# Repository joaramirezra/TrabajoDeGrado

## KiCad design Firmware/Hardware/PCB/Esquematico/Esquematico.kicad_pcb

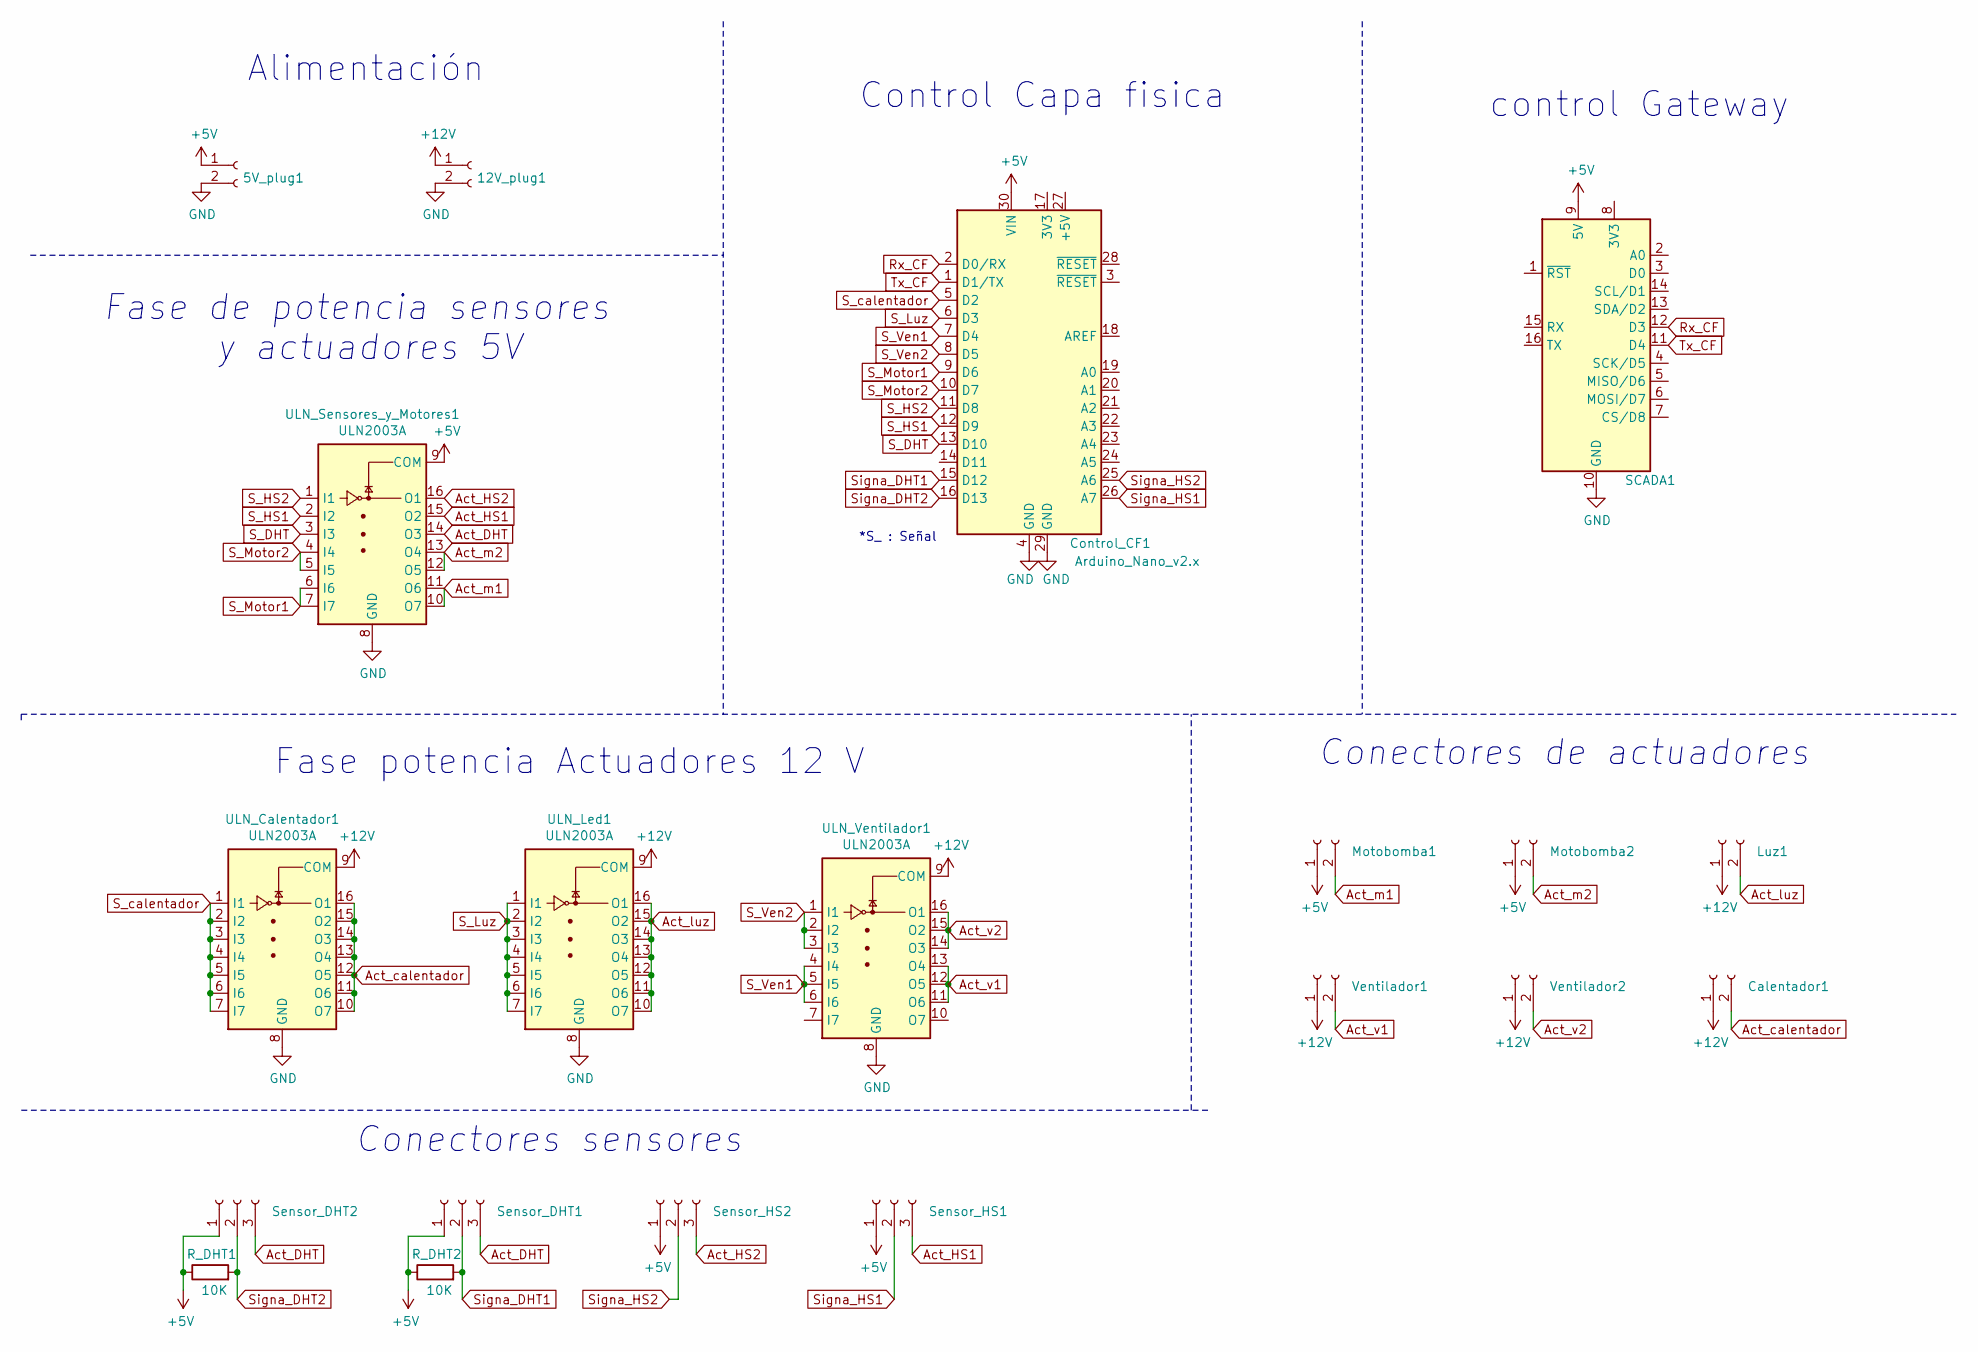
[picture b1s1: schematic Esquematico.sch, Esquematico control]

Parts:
5V_plug1, 12V_plug1: Conn_01x02_Female; TerminalBlock_bornier-2_P5.08mm
Calentador1: Conn_01x02_Female; TerminalBlock_bornier-2_P5.08mm
Control_CF1: Arduino_Nano_v2.x; Arduino_Nano
Luz1: Conn_01x02_Female; TerminalBlock_bornier-2_P5.08mm
Motobomba1, Motobomba2: Conn_01x02_Female; TerminalBlock_bornier-2_P5.08mm
R_DHT1, R_DHT2: 10K; R_Axial_DIN0207_L6.3mm_D2.5mm_P7.62mm_Horizontal
SCADA1: WeMos_D1_mini; WEMOS_D1_mini_light
Sensor_DHT1, Sensor_DHT2: Conn_01x03_Female; TerminalBlock_bornier-3_P5.08mm
Sensor_HS1, Sensor_HS2: Conn_01x03_Female; TerminalBlock_bornier-3_P5.08mm
ULN_Calentador1: ULN2003A; DIP-16_W7.62mm_LongPads
ULN_Led1: ULN2003A; DIP-16_W7.62mm_LongPads
ULN_Sensores_y_Motores1: ULN2003A; DIP-16_W7.62mm_LongPads
ULN_Ventilador1: ULN2003A; DIP-16_W7.62mm_LongPads
Ventilador1, Ventilador2: Conn_01x02_Female; TerminalBlock_bornier-2_P5.08mm

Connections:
+5V: 5V_plug1.1, Control_CF1.30 (VIN), Motobomba1.1, Motobomba2.1, R_DHT1.1, R_DHT2.1, SCADA1.9 (5V), Sensor_DHT1.1, Sensor_DHT2.1, Sensor_HS1.1, Sensor_HS2.1, ULN_Sensores_y_Motores1.9 (COM); also elsewhere on the board
+12V: 12V_plug1.1, Calentador1.1, Luz1.1, ULN_Calentador1.9 (COM), ULN_Led1.9 (COM), ULN_Ventilador1.9 (COM), Ventilador1.1, Ventilador2.1
Act_DHT: Sensor_DHT1.3, Sensor_DHT2.3, ULN_Sensores_y_Motores1.14 (O3); also elsewhere on the board
Act_HS1: Sensor_HS1.3, ULN_Sensores_y_Motores1.15 (O2); also elsewhere on the board
Act_HS2: Sensor_HS2.3, ULN_Sensores_y_Motores1.16 (O1); also elsewhere on the board
Act_calentador: Calentador1.2, ULN_Calentador1.10 (O7), ULN_Calentador1.11 (O6), ULN_Calentador1.12 (O5), ULN_Calentador1.13 (O4), ULN_Calentador1.14 (O3), ULN_Calentador1.15 (O2), ULN_Calentador1.16 (O1)
Act_luz: Luz1.2, ULN_Led1.10 (O7), ULN_Led1.11 (O6), ULN_Led1.12 (O5), ULN_Led1.13 (O4), ULN_Led1.14 (O3), ULN_Led1.15 (O2), ULN_Led1.16 (O1)
Act_m1: Motobomba1.2, ULN_Sensores_y_Motores1.10 (O7), ULN_Sensores_y_Motores1.11 (O6); also elsewhere on the board
Act_m2: Motobomba2.2, ULN_Sensores_y_Motores1.12 (O5), ULN_Sensores_y_Motores1.13 (O4); also elsewhere on the board
Act_v1: ULN_Ventilador1.11 (O6), ULN_Ventilador1.12 (O5), ULN_Ventilador1.13 (O4), Ventilador1.2
Act_v2: ULN_Ventilador1.14 (O3), ULN_Ventilador1.15 (O2), ULN_Ventilador1.16 (O1), Ventilador2.2
GND: 5V_plug1.2, 12V_plug1.2, Control_CF1.4 (GND), Control_CF1.29 (GND), SCADA1.10 (GND), ULN_Calentador1.8 (GND), ULN_Led1.8 (GND), ULN_Sensores_y_Motores1.8 (GND), ULN_Ventilador1.8 (GND); also elsewhere on the board
Rx_CF: Control_CF1.2 (D0/RX), SCADA1.12 (D3)
S_DHT: Control_CF1.13 (D10), ULN_Sensores_y_Motores1.3 (I3); also elsewhere on the board
S_HS1: Control_CF1.12 (D9), ULN_Sensores_y_Motores1.2 (I2); also elsewhere on the board
S_HS2: Control_CF1.11 (D8), ULN_Sensores_y_Motores1.1 (I1); also elsewhere on the board
S_Luz: Control_CF1.6 (D3), ULN_Led1.1 (I1), ULN_Led1.2 (I2), ULN_Led1.3 (I3), ULN_Led1.4 (I4), ULN_Led1.5 (I5), ULN_Led1.6 (I6), ULN_Led1.7 (I7)
S_Motor1: Control_CF1.9 (D6), ULN_Sensores_y_Motores1.6 (I6), ULN_Sensores_y_Motores1.7 (I7); also elsewhere on the board
S_Motor2: Control_CF1.10 (D7), ULN_Sensores_y_Motores1.4 (I4), ULN_Sensores_y_Motores1.5 (I5); also elsewhere on the board
S_Ven1: Control_CF1.7 (D4), ULN_Ventilador1.4 (I4), ULN_Ventilador1.5 (I5), ULN_Ventilador1.6 (I6)
S_Ven2: Control_CF1.8 (D5), ULN_Ventilador1.1 (I1), ULN_Ventilador1.2 (I2), ULN_Ventilador1.3 (I3)
S_calentador: Control_CF1.5 (D2), ULN_Calentador1.1 (I1), ULN_Calentador1.2 (I2), ULN_Calentador1.3 (I3), ULN_Calentador1.4 (I4), ULN_Calentador1.5 (I5), ULN_Calentador1.6 (I6), ULN_Calentador1.7 (I7)
Signa_DHT1: Control_CF1.15 (D12), R_DHT2.2, Sensor_DHT1.2
Signa_DHT2: Control_CF1.16 (D13), R_DHT1.2, Sensor_DHT2.2
Signa_HS1: Control_CF1.26 (A7), Sensor_HS1.2
Signa_HS2: Control_CF1.25 (A6), Sensor_HS2.2
Tx_CF: Control_CF1.1 (D1/TX), SCADA1.11 (D4)

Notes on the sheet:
*S_ : Señal
Alimentación
Fase potencia Actuadores 12 V
Control Capa fisica
Conectores sensores
control Gateway
Conectores de actuadores
Fase de potencia sensores y actuadores 5V

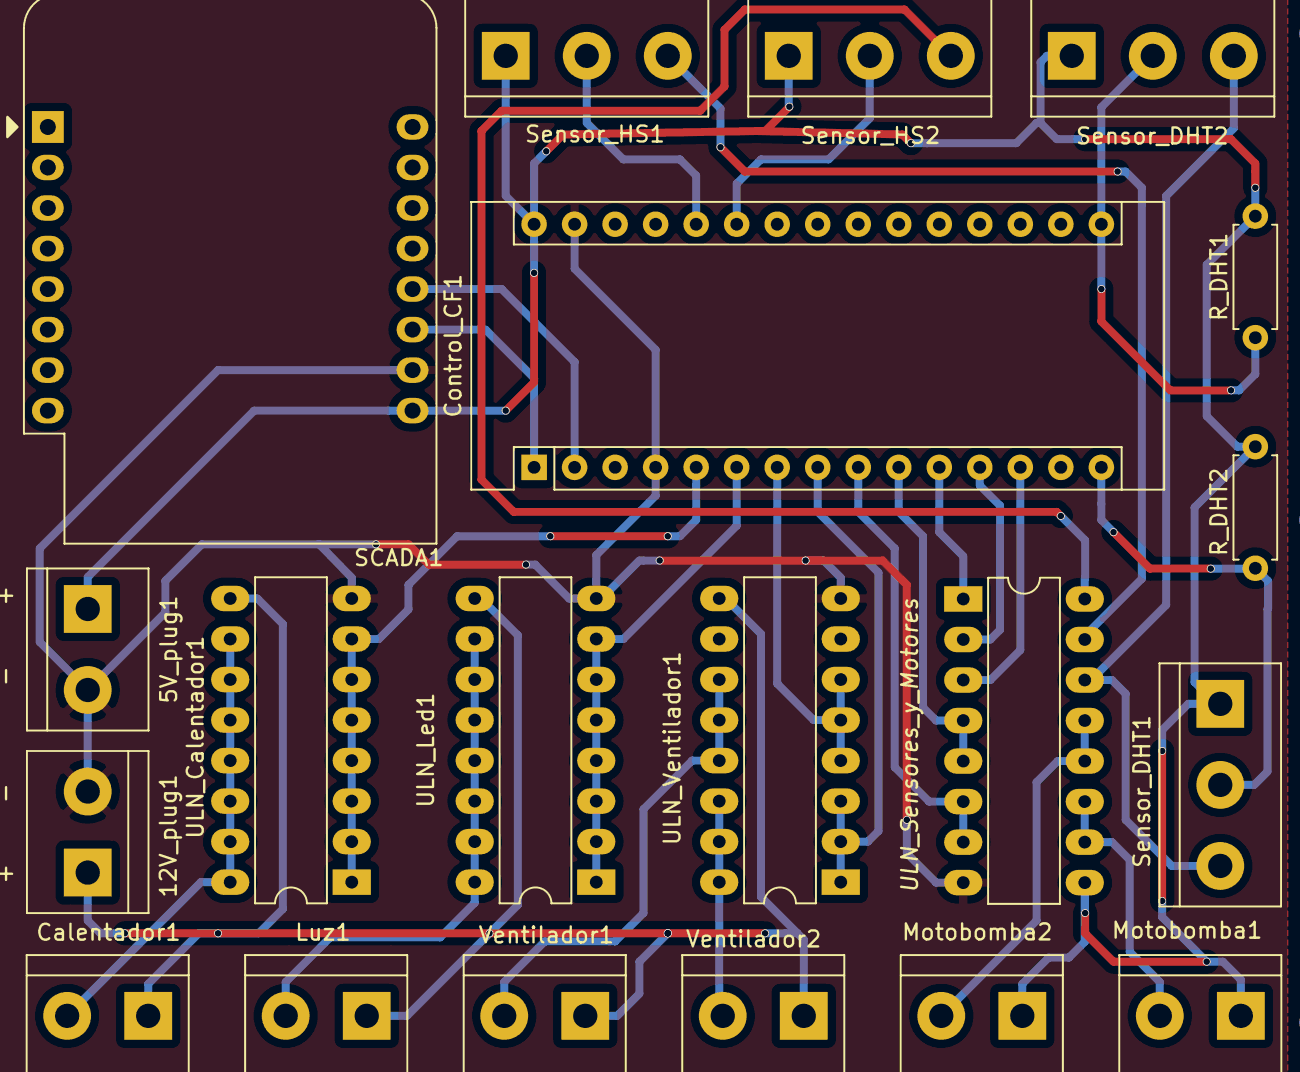
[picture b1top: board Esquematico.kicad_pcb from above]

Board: 2 copper layers, 20 parts (0 on the bottom side), 27 nets.

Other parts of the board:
ULN_Sensores_y_Motores: ULN2003A; DIP-16_W7.62mm_LongPads

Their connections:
+5V: ULN_Sensores_y_Motores.9; also elsewhere on the board
Act_DHT: ULN_Sensores_y_Motores.14; also elsewhere on the board
Act_HS1: ULN_Sensores_y_Motores.15; also elsewhere on the board
Act_HS2: ULN_Sensores_y_Motores.16; also elsewhere on the board
Act_m1: ULN_Sensores_y_Motores.10, ULN_Sensores_y_Motores.11; also elsewhere on the board
Act_m2: ULN_Sensores_y_Motores.12, ULN_Sensores_y_Motores.13; also elsewhere on the board
GND: ULN_Sensores_y_Motores.8; also elsewhere on the board
S_DHT: ULN_Sensores_y_Motores.3; also elsewhere on the board
S_HS1: ULN_Sensores_y_Motores.2; also elsewhere on the board
S_HS2: ULN_Sensores_y_Motores.1; also elsewhere on the board
S_Motor1: ULN_Sensores_y_Motores.6, ULN_Sensores_y_Motores.7; also elsewhere on the board
S_Motor2: ULN_Sensores_y_Motores.4, ULN_Sensores_y_Motores.5; also elsewhere on the board

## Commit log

2020-06-30 ver1
